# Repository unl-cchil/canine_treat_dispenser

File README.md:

# Computer-controlled dog treat dispenser

**This project retrofits an existing off-the-shelf dog treat dispenser with new electronics that allow it to be controlled by a computer.**

### Overview

When performing canine operant conditioning studies, the delivery of the reward can be a limiting factor of the study. While there are a few commercially available options for automatically delivering rewards, they generally require manual input, such as using a remote control, in accordance with the experiment script. This means that human reaction times and transmission distances can cause interruptions to the flow of the experiment. The potential for development of non-supervised conditioning studies is limited by this same factor. To remedy this, we retrofitted an off-the-shelf treat dispenser with new electronics that allow it to be remotely controllable as well as act as an experiment computation, data storage, and networking center. We present a fully integrated dispenser driver board with a complementary Raspberry Pi. With rather simple modifications, the commercial treat dispenser can be modified into a computer-controlled dispenser for canine cognition experiments or for other forms of canine training or games.

[Demonstration video](https://www.youtube.com/watch?v=veKvqE5ipu4)

### License

The software and hardware designs are available under a [Creative Commons Attribution-ShareAlike 4.0 International Public License (CC BY-SA 4.0)](https://creativecommons.org/licenses/by-sa/4.0/). You are free to:

* Share — copy and redistribute the material in any medium or format
* Adapt — remix, transform, and build upon the material for any purpose, even commercially.

Under the following terms:

* Attribution — You must give appropriate credit, provide a link to the license, and indicate if changes were made. You may do so in any reasonable manner, but not in any way that suggests the licensor endorses you or your use.
* ShareAlike — If you remix, transform, or build upon the material, you must distribute your contributions under the same license as the original.

### Contact

This project was conducted by the [Canine Cognition and Human Interaction Lab](https://dogcog.unl.edu) and funded by the [National Science Foundation](https://nsf.gov). For questions, please contact the developer Walker Arce (warce@unomaha.edu) or the principal investigator Jeffrey R. Stevens (jeffrey.r.stevens@gmail.com).

### Citation
Arce, W., & Stevens, J. R. (2020). Developing a computer-controlled treat dispenser for canine operant conditioning. _Journal of Open Hardware_, 4(1), 6. https://doi.org/10.5334/joh.27

### Project Mentions
[Hackaday](https://hackaday.com/2020/10/31/using-open-source-to-train-your-dog/)

[Open Neuroscience](https://open-neuroscience.com/post/computer_controlled_dog_treat_dispenser/)

### Dataset Metadata
The following table is necessary for this dataset to be indexed by search
engines such as <a href="https://g.co/datasetsearch">Google Dataset Search</a>.
<div itemscope itemtype="http://schema.org/Dataset">
<table>
<tr>
<th>property</th>
<th>value</th>
</tr>
<tr>
<td>name</td>
<td><code itemprop="name">Computer-controlled dog treat dispenser reliability testing dataset</code></td>
</tr>
<tr>
<td>description</td>
<td><code itemprop="description">The dataset from the paper [Developing a computer-controlled treat dispenser for canine operant conditioning](https://doi.org/10.5334/joh.27). We tested two treat dispensers 100 times each with 10 tests of increasing dispensing targets from 1 to 10 treats. Each row of the data file gives the expected and actual number of treats dispensed for a single trial.</code></td>
</tr>
</tr>
<tr>
<td>url</td>
<td><code itemprop="url">https://github.com/unl-cchil/canine_treat_dispenser</code></td>
</tr>
<tr>
<td>sameAs</td>
<td><code itemprop="sameAs">https://github.com/unl-cchil/canine_treat_dispenser</code></td>
</tr>
<tr>
<td>citation</td>
<td><code itemprop="citation">https://doi.org/10.5334/joh.27</code></td>
</tr>
<tr>
<td>license</td>
<td>
<div itemscope itemtype="http://schema.org/CreativeWork" itemprop="license">
<table>
<tr>
<th>property</th>
<th>value</th>
</tr>
<tr>
<td>name</td>
<td><code itemprop="name">CC BY-SA 4.0</code></td>
</tr>
<tr>
<td>url</td>
<td><code itemprop="url">https://creativecommons.org/licenses/by-sa/4.0/</code></td>
</tr>
</table>
</div>
</td>
</tr>
</table>
</div>

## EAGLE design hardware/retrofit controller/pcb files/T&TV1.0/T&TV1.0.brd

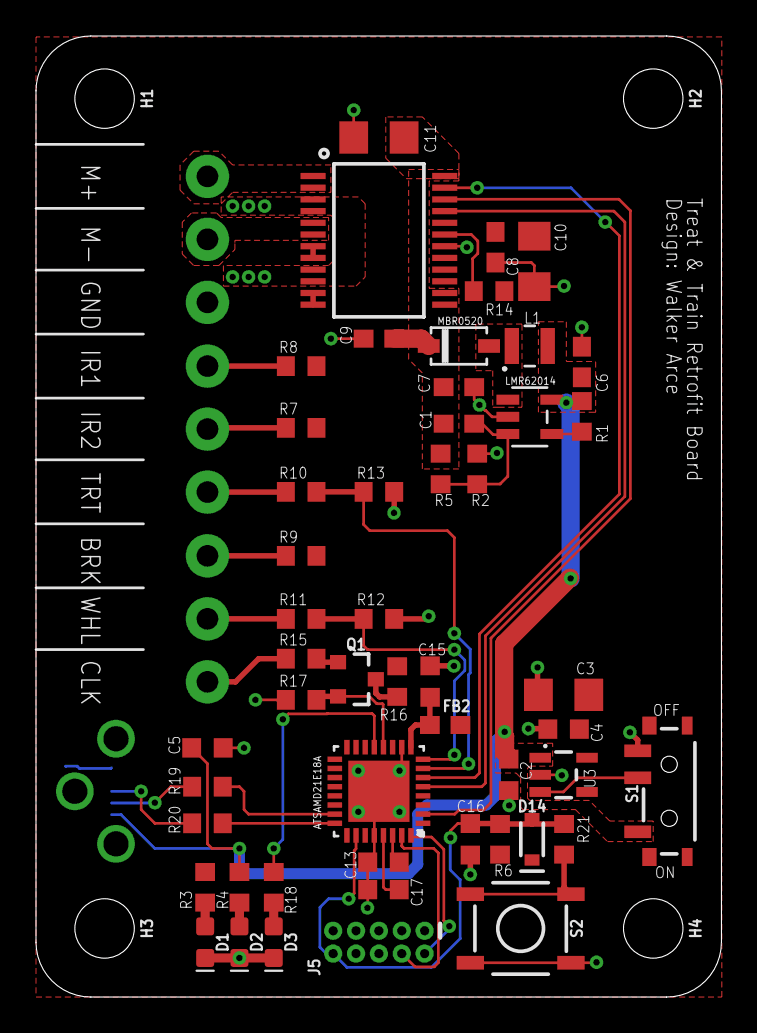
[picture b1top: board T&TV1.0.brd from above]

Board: 2 copper layers, 38.1 x 53.4 mm, 59 parts (1 on the bottom side), 41 nets.

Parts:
C1: 220p; C0603
C2, C4, C5, C13, C15, C16, C17: 0.1u; C0603K
C3, C10, C11: 10u; C1206
C6: 2.2u; C0603
C7: 4.7u; C0603
C8, C9: 0.1u; C0603
D1, D2, D3: RED; LED-0603
D14: 250mA/100V; SOD-323
FB2: 30Ω/1.8A; 0603
H1, H2, H3, H4: STAND-OFF
J1: 105133-0001; MOLEX_105133-0001
J2, J3, J4: SCREWTERMINAL-3.5MM-3-NS
J5: CORTEX_DEBUG_PTH; 2X5-PTH-1.27MM
L1: 1239AS-H-100M=P2; IND_DFE252012C
Q1: 600mA/40V; SOT23-3
R1: 51k; R0603
R2: 13.3k; R0603
R3, R4, R7, R8, R9, R18, R21: 330; R0603
R5: 117k; R0603
R6, R14, R15, R17: 10k; R0603
R10, R11, R12, R13: 1M; R0603
R16: 1k; R0603
R19, R20: 22; R0603
S1: SWITCH_SPST_SMD_A
S2: TACTILE_SWITCH_SMD_5.2MM
U1: LMR62014XMFE/NOPB; MF05A
U3: 3.3V; SOT23-5
U4: MBR0520; SOD-123
U5: ATSAMD21E18A; QFN32_5X5MC
U$1: TB6612FNG; SSOP24

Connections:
3.3V: C3.1, C4.1, C8.1, C10.1, C13.1, D14.C, FB2.2, J5.1, R3.1, R6.2, R7.1, R8.1, R9.1, R14.2, R16.1, U3.5, U5.30, U$1.20
12V: C1.2, C7.1, C9.1, C11.1, R5.1, U4.2, U$1.13, U$1.14, U$1.24
!RESET: C16.1, D14.A, J5.10, R6.1, R21.1, U5.26
!SHDN: R1.1, U1.4
A1: J2.1, U$1.1, U$1.2
A2: J2.2, U$1.5, U$1.6
AIN1: U5.5, U$1.21
AIN2: U5.2, U$1.22
B1: U$1.11, U$1.12
B2: U$1.7, U$1.8
BOOT: R18.1, U5.13
CLICK: Q1.2, R17.1, U5.12
D+: J1.3, R20.1
D-: J1.2, R19.1
GND: C2.2, C3.2, C4.2, C5.2, C6.2, C7.2, C8.2, C9.2, C10.2, C11.2, C13.2, C15.2, C16.2, C17.2, D1.C, D2.C, D3.C, J1.5, J1.P$1, J1.P$2, J1.P$3, J2.3, J5.3, J5.5, R2.1, R12.1, R13.1, R17.2, S1.1, S2.1, S2.2, U1.2, U3.2, U5.10, U5.28, U5.33, U$1.3, U$1.4, U$1.9, U$1.10, U$1.18
unnamed: D1.A, R3.2
unnamed: Q1.1, R15.2
unnamed: L1.1, U1.1, U4.1
unnamed: C15.1, FB2.1, U5.9
unnamed: J3.1, R8.2
unnamed: J3.2, R7.2
unnamed: C1.1, R2.2, R5.2, U1.3
unnamed: J4.1, R9.2
unnamed: C17.1, U5.29
unnamed: J3.3, R10.2
unnamed: Q1.3, R16.2
unnamed: D2.A, R4.2
unnamed: J4.2, R11.2
unnamed: J4.3, R15.1
unnamed: D3.A, R18.2
unnamed: R20.2, U5.24
unnamed: R19.2, U5.23
unnamed: R21.2, S2.3, S2.4
unnamed: S1.2, U3.3
PWMA: U5.6, U$1.23
STBY: R14.1, U$1.19
SWDCLK: J5.4, U5.31
SWDIO: J5.2, U5.32
TREAT: R10.1, R13.2, U5.7
V_USB: C2.1, C5.1, C6.1, J1.1, L1.2, R1.2, R4.1, S1.3, U1.5, U3.1
WHEEL: R11.1, R12.2, U5.8

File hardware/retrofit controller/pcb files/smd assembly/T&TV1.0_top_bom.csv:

Comment,Designator,Footprint,LCSC Part #
0.1u,S1 S2 C2 C4 C5,C0603K,
0.1u,C8 C9,C0603,
0.1u,C13 C15 C16 C17,C0603K,
1M,R10 R11 R12 R13,R0603,
1k,R16,R0603,
2.2u,C6,C0603,
3.3V,U3,SOT23-5,
4.7u,C7,C0603,
10k,R6 R14 R15 R17,R0603,
10u,C3 C10 C11,C1206,
13.3k,R2,R0603,
22,R19 R20,R0603,
30Ω/1.8A,FB2,0603,
51k,R1,R0603,
117k,R5,R0603,
220p,C1,C0603,
250mA/100V,D14,SOD-323,
330,R3 R4 R7 R8 R9 R18 R21,R0603,
600mA/40V,Q1,SOT23-3,
1239AS-H-100M=P2,L1,IND_DFE252012C,
ATSAMD21E18A,U5,QFN32_5X5MC,
LMR62014XMFE/NOPB,U1,MF05A,
MBR0520,U4,SOD-123,
RED,D1 D2 D3,LED-0603,
TB6612FNG,U$1,SSOP24,

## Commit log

2020-07-22 Add Figure 2
2020-07-23 Updated files
    Added python driver
    Added both Arduino firmwares
    Added gerbers and renders
2020-07-28 Add README and license
2020-07-28 Updated file structure for repo
2020-07-28 Adjust license
2020-07-31 Updated a line in the BOM descriptions
2020-09-29 Rename and revise data and R script
    - Rename files
    - Rename trial column of data file
    - Add preamble to R script
    - Clean up R script
    - Create README file
2020-10-28 Add citation and journal article
2020-10-31 Add demonstration video link to README
2020-12-11 Added SMT assembly files
    Generated by: https://github.com/oxullo/jlcpcb-eagle
2021-12-13 Add schema.org dataset metadata

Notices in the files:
parts and their libraries:
SparkFun-LED: Licensing: Creative Commons ShareAlike 4.0 International - https://creativecommons.org/licenses/by-sa/4.0
COPYRIGHT: Copyright (C) 2016 Accelerated Designs. All rights reserved
COPYRIGHT: Copyright (C) 2018 Accelerated Designs. All rights reserved
